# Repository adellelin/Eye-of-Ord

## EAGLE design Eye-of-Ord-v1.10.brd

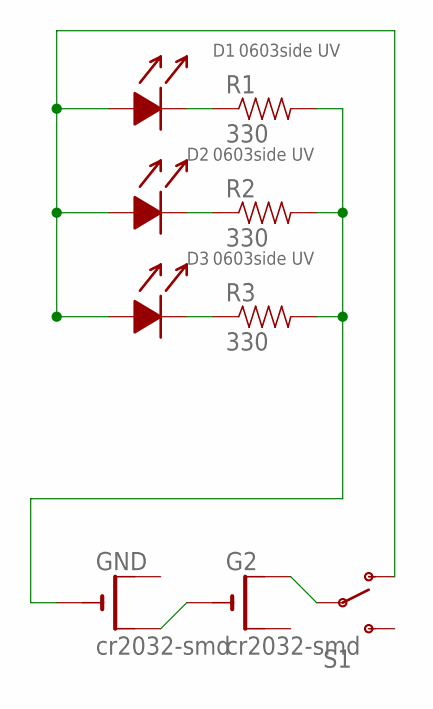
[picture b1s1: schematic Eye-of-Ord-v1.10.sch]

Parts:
D1, D2, D3: 0603side UV; SMD-0603-LED-SIDE
G2: cr2032-smd; CR2032-SMD; DIGIKEY_PART_ID BK-913-ND
GND: cr2032-smd; CR2032-SMD; DIGIKEY_PART_ID BK-913-ND
R1, R2, R3: 330; 0603-RES; DIGIKEY_PART_ID P100BZCT-ND
S1: SWITCH-SPDT-SMD-A; SWITCH-SPST-SMD-A; DIGIKEY_PART_ID 679-1847-1-ND

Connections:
GND: GND.-, R1.2, R2.2, R3.2
unnamed: G2.-, GND.+$2 (+1)
unnamed: D2.C (K), R2.1
unnamed: D3.C (K), R3.1
unnamed: D1.C (K), R1.1
unnamed: G2.+$1 (+), S1.2
VCC: D1.A, D2.A, D3.A, S1.1 (O)

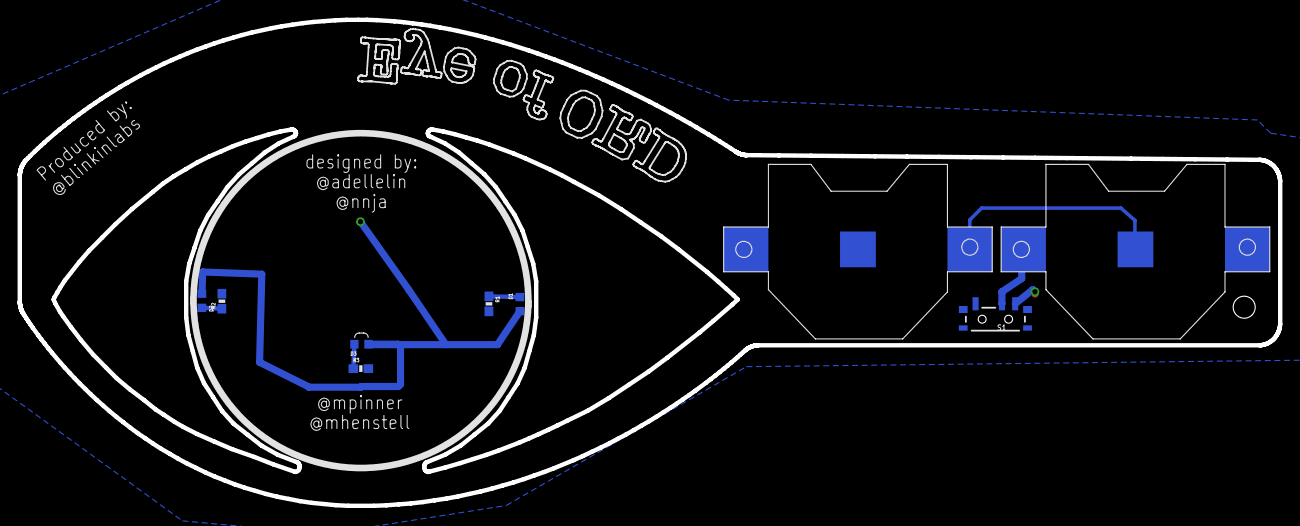
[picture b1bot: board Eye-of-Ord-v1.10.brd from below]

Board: 2 copper layers, 143.0 x 55.2 mm, 9 parts (9 on the bottom side), 7 nets.

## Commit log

2019-11-23 first pass to get quote
2019-11-24 baord sketches
2019-12-01 latest board for test print
2019-12-01 updated with latest illustrator
2019-12-03 Added more aesthetic lines and fonts + DXFs
2019-12-03 made board more narrow
2019-12-03 fixed ground error and line thickness, added dxf ulp

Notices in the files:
parts and their libraries:
SparkFun-Resistors: Licensing: Creative Commons ShareAlike 4.0 International - https://creativecommons.org/licenses/by-sa/4.0
